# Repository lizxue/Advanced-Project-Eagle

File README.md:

# Advanced-Project-Eagle
PCB schematic and board design for a quadcopter

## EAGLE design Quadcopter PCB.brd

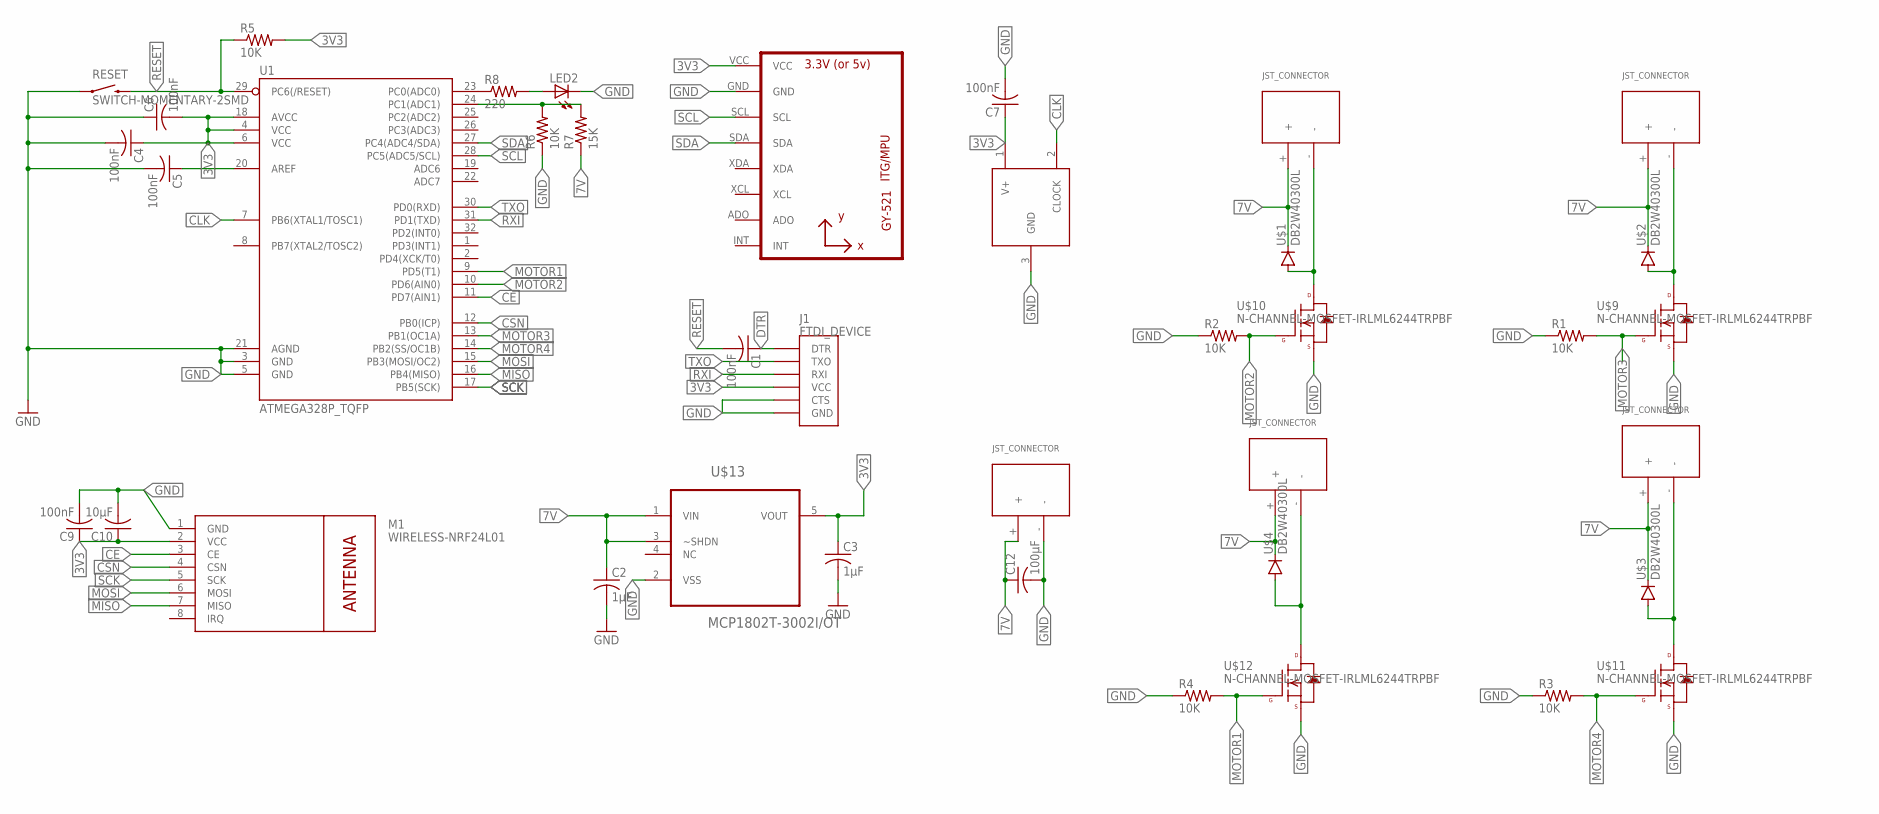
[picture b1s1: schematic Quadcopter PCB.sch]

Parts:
AXR1: MAX7375; SC70-3L
BATTERYJSTCONNECTOR: JST_CONNECTOR_FEMALE
C1, C4, C5, C6, C7, C9: 100nF; C0603
C2, C3: 1µF; C0603
C10: 10µF; C0603
C12: 100µF; C1210
J1: FTDI_DEVICE; FTDI_DEVICE_SIDE
LED2: LEDCHIP-LED0603; CHIP-LED0603
M1: WIRELESS-NRF24L01
R1, R2, R3, R4, R5, R6: 10K; R0603
R7: 15K; R0603
R8: 220; R0603
RESET: SWITCH-MOMENTARY-2SMD; TACTILE-SWITCH-SMD
U1: ATMEGA328P_TQFP; TQFP32-08
U2: GY-521MPU6050; GY-521
U$1, U$2, U$3, U$4: DB2W40300L; MINI2-F3-B
U$5, U$6, U$7, U$8: JST_CONNECTOR_FEMALE
U$9, U$10, U$11, U$12: N-CHANNEL-MOSFET-IRLML6244TRPBF; SOT23-3
U$13: MCP1802T-3002I/OT; SOT95P270X145-5N

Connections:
3V3: AXR1.1 (V+), C3.1, C4.1, C5.1, C6.2, C7.1, C9.1, C10.1, J1.P$4 (VCC), M1.2 (VCC), R5.2, U1.4 (VCC), U1.6 (VCC), U1.18 (AVCC), U1.20 (AREF), U2.VCC, U$13.5 (VOUT)
7V: BATTERYJSTCONNECTOR.+, C2.1, C12.1, R7.1, U$1.NEG (GPIN), U$2.NEG (GPIN), U$3.NEG (GPIN), U$4.NEG (GPIN), U$5.+, U$6.+, U$7.+, U$8.+, U$13.1 (VIN), U$13.3 (~SHDN)
CE: M1.3 (CE), U1.11 (PD7(AIN1))
CLK: AXR1.2 (CLOCK), U1.7 (PB6(XTAL1/TOSC1))
CSN: M1.4 (CSN), U1.12 (PB0(ICP))
DTR: C1.1, J1.P$1 (DTR)
GND: AXR1.3 (GND), BATTERYJSTCONNECTOR.-, C2.2, C3.2, C4.2, C5.2, C6.1, C7.2, C9.2, C10.2, C12.2, J1.P$5 (CTS), J1.P$6 (GND), LED2.C, M1.1 (GND), R1.1, R2.1, R3.1, R4.1, R6.1, RESET.1, U1.3 (GND), U1.5 (GND), U1.21 (AGND), U2.GND, U$9.2 (S), U$10.2 (S), U$11.2 (S), U$12.2 (S), U$13.2 (VSS)
MISO: M1.7 (MISO), U1.16 (PB4(MISO))
MOSI: M1.6 (MOSI), U1.15 (PB3(MOSI/OC2))
MOTOR1: R4.2, U1.9 (PD5(T1)), U$12.1 (G)
MOTOR2: R2.2, U1.10 (PD6(AIN0)), U$10.1 (G)
MOTOR3: R1.2, U1.13 (PB1(OC1A)), U$9.1 (G)
MOTOR4: R3.2, U1.14 (PB2(SS/OC1B)), U$11.1 (G)
unnamed: R6.2, R7.2, U1.24 (PC1(ADC1))
unnamed: R8.1, U1.23 (PC0(ADC0))
unnamed: LED2.A, R8.2
unnamed: U$1.POS (PPIN), U$6.-, U$10.3 (D)
unnamed: U$2.POS (PPIN), U$7.-, U$9.3 (D)
unnamed: U$3.POS (PPIN), U$8.-, U$11.3 (D)
unnamed: U$4.POS (PPIN), U$5.-, U$12.3 (D)
RESET: C1.2, R5.1, RESET.3 (2), U1.29 (PC6(/RESET))
RXI: J1.P$3 (RXI), U1.31 (PD1(TXD))
SCK: M1.5 (SCK), U1.17 (PB5(SCK))
SCL: U1.28 (PC5(ADC5/SCL)), U2.SCL
SDA: U1.27 (PC4(ADC4/SDA)), U2.SDA
TXO: J1.P$2 (TXO), U1.30 (PD0(RXD))

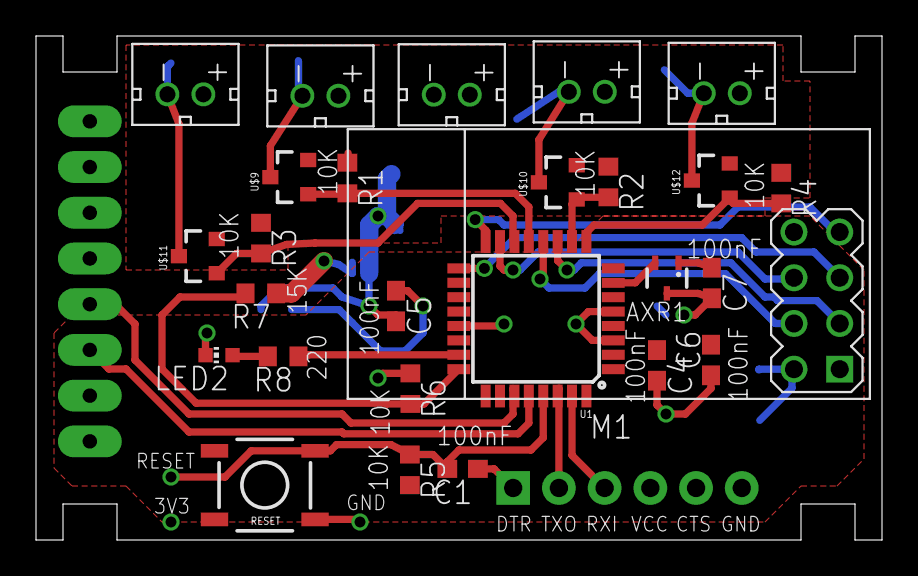
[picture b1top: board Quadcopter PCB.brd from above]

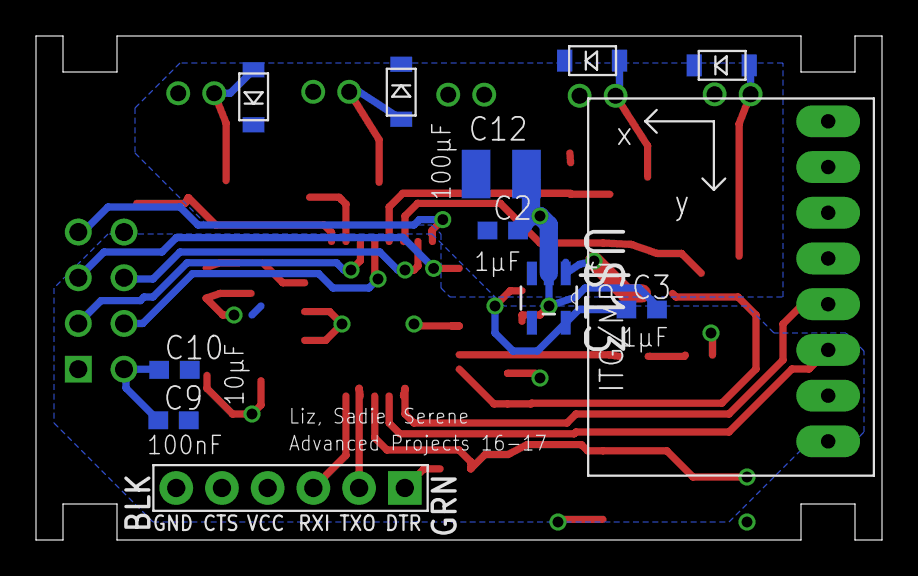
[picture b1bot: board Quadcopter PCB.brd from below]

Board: 2 copper layers, 47.0 x 28.0 mm, 39 parts (12 on the bottom side), 26 nets.
